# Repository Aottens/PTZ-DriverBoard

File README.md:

# PTZ driver board

A driver board for PTZ camera heads and its firmware, designed together: one print that can drive any head.

## Status
Rev B of the board is designed and checked, and ready for a JLC quote: a cheap two-layer carrier for plug-in
drivers, MCU and Ethernet, estimated at €68 to €90 for five assembled boards. It is not ordered and not measured.
Rev A, which would have cost almost €400, is under the git tag `rev-a`. There is no firmware yet.
The test rig for the mechanics is modelled, not printed.
Plan in `BACKLOG.md`, handoff in `STATE.md`, decisions in `DECISIONS.md`.

## What works today
- `hardware/`: the KiCad 10 project of Rev B, generated by the scripts in `hardware/tools/`, with BOM, placement file
  and Gerbers for JLCPCB in `hardware/fab/`. How to rebuild it: `hardware/README.md`. What to buy and solder:
  `hardware/ASSEMBLY.md`.
- Checks that run on any machine with KiCad 10: `hardware/check_netlist.py` (every pin against the specs),
  `hardware/check_board.py` (every number in `specs/modules/board.md`, ERC and DRC), `hardware/check_fit.py`
  (the board with its modules and plugs in the base).
- `hardware/calc/`: the power calculations and the cost estimate of one JLC order, from the real BOM.
- `tests/hardware/bringup-rev-b.md`: the current-limited first power-up, for the owner to run on the real board.
- `mechanica/rig/`: the test rig model and its checks.

## How work happens
Spec → test → build → review, one build per PR; see `CLAUDE.md`.

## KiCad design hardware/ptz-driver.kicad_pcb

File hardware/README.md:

# hardware/

The driver board, Rev B: a two-layer carrier for plug-in modules. The specs in `specs/modules/` say what each part
is for; this says how the files are made. Rev A, the four-layer board with its drivers on board, is under the git
tag `rev-a` (`git show rev-a:hardware/README.md`).

## What is where

| File | What |
| --- | --- |
| `ptz-driver.kicad_pro`, `.kicad_sch`, `.kicad_pcb` and the sheet files | The KiCad 10 project. Open it in KiCad to look; change it through the scripts |
| `tools/circuit.py` | The circuit as data: every part, net, footprint and LCSC number. Writes the schematic |
| `../firmware/include/pins.h` | The one place MCU pins are assigned |
| `tools/make_libs.py`, `ptz.pretty/` | The project's footprints: the three module sockets, the 5 V regulator, the test point |
| `tools/placement.py` | Where every part sits, and the copper laid before routing: the supply path, the motor outputs |
| `tools/board.py`, `tools/silk.py` | The board build (place, dsn, ses, finish) and the silkscreen |
| `route/run.sh`, `tools/complete.py`, `tools/widen.py` | Routing from scratch: Freerouting, then the grid router that closes what it leaves open and stitches the ground pours, then supply tracks widened where the routers necked them |
| `tools/project.py` | Design rules and net classes (KiCad rewrites the project file, so they live here) |
| `check_netlist.py` | Expected pin-to-net table per criterion, written from the specs without the schematic |
| `check_board.py` | Every number `specs/modules/board.md` states, plus ERC and DRC |
| `tools/groundcut.py` | The narrowest cross-section of ground copper between two groups of pads (BRD-13), used by `check_board.py` |
| `check_fit.py` | The board with its modules, heat sinks and plugs in the working envelope |
| `calc/power.py`, `calc/cost.py` | The calculations, with every input and its source |
| `fab/make_jlc.py`, `fab/jlc/`, `fab/gerbers/` | BOM and placement file fitted on JLC's own footprints, and the Gerbers |
| `fab/jlc_pins.py`, `fab/jlc_pins.md` | What JLC's own library calls each pin of every polar part, against the board's nets |
| `sourcing/` | JLC's parts API (`jlc_api.py`) and the check table per BOM line (`jlc_check.md`) |
| `sourcing/owner_bom.py`, `owner_bom.md`, `owner_bom_reichelt.csv` | The owner's shopping list for everything JLC does not assemble, from the schematic, with Reichelt's article numbers and prices |
| `review/` | The blind review and what was done with it |
| `ASSEMBLY.md`, `BUILD_NOTES.md`, `datasheets/README.md` | What the owner buys, solders and plugs; lessons; datasheet sources and revisions |

## Rebuilding from scratch

`KP` is KiCad's Python: `/Applications/KiCad/KiCad.app/Contents/Frameworks/Python.framework/Versions/Current/bin/python3`.
Run from `hardware/`.

1. `python3 tools/make_libs.py`: project footprints, library tables, project rules.
2. `python3 tools/circuit.py`: the schematic. It reads the netlist back through KiCad and stops if it differs.
3. `python3 check_netlist.py`
4. `sh route/run.sh`: places every part, routes, finishes the board and widens its supply tracks, about five minutes. **This discards the
   routing**, and Freerouting is not repeatable: a rerun gives another board. What was done by hand on the board
   in this repository afterwards is in `BUILD_NOTES.md` under *How the routed board was made*.
5. `$KP check_board.py` and `$KP check_fit.py`
6. `$KP fab/make_jlc.py`, `python3 sourcing/jlc_read.py`, `python3 fab/jlc_pins.py > fab/jlc_pins.md`,
   `python3 calc/cost.py`, and the Gerbers with `sh fab/make_gerbers.sh`.

A change that keeps the placement and the nets (a value, an LCSC number) needs only steps 2, 3 and 6, but the
footprint fields on the board then lag the schematic until step 4: `check_board.py` reports that as a parity
issue. `$KP tools/board.py finish` alone redraws the silkscreen and the top ground pour on the routed board.

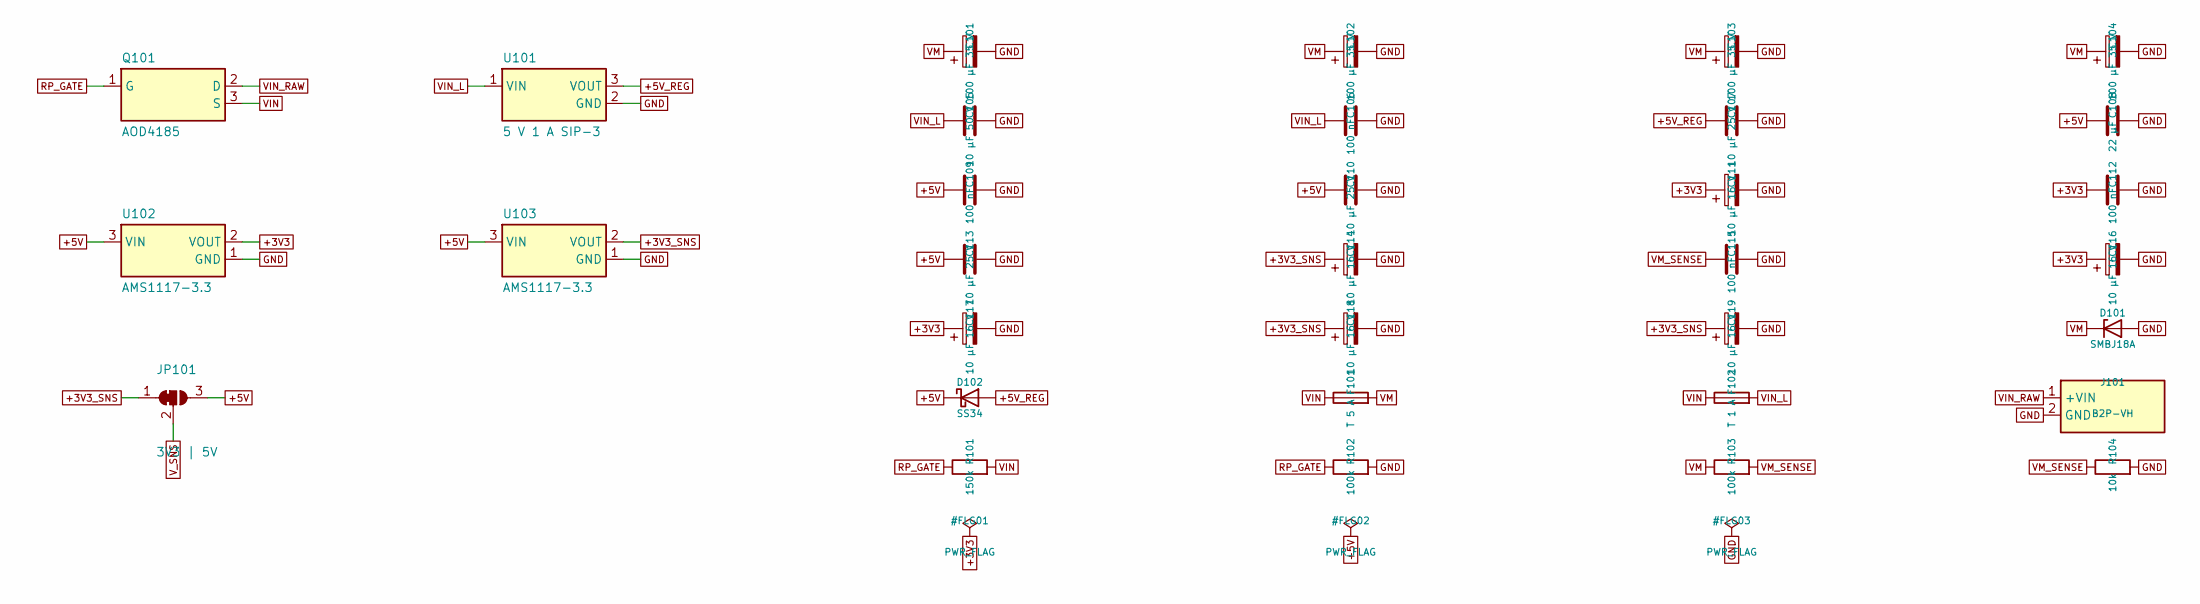
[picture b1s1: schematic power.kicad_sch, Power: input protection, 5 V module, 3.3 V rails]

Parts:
C101, C102, C103, C104: 100 µF 35 V; CP_Radial_D6.3mm_P2.50mm
C105: 10 µF 50 V; C_1206_3216Metric; LCSC C13585
C106, C109, C112, C115: 100 nF; C_0603_1608Metric; LCSC C14663
C107, C110, C113: 10 µF 25 V; C_0805_2012Metric; LCSC C15850
C108: 22 µF; C_0805_2012Metric; LCSC C45783
C111, C114, C116, C117, C118, C119: 10 µF 16 V; CP_EIA-3216-18_Kemet-A; MPN TAJA106K016RNJ; LCSC C7171
D101: SMBJ18A; D_SMB; MPN SMBJ18A; LCSC C19077573
D102: SS34; D_SMA; MPN SS34; LCSC C8678
F101: T 5 A; Fuseholder_TR5_Littelfuse_No560_No460
F102: T 1 A; Fuseholder_TR5_Littelfuse_No560_No460
J101: B2P-VH; JST_VH_B2P-VH_1x02_P3.96mm_Vertical
JP101: 3V3 | 5V; SolderJumper-3_P1.3mm_Bridged12_RoundedPad1.0x1.5mm
Q101: AOD4185; TO-252_JLC; MPN AOD4185; LCSC C400894
R101: 150k; R_0603_1608Metric; LCSC C22807
R102, R103: 100k; R_0603_1608Metric; LCSC C25803
R104: 10k; R_0603_1608Metric; LCSC C25804
U101: 5 V 1 A SIP-3; SIP3_DCDC_7805
U102, U103: AMS1117-3.3; SOT-223-3_TabPin2; MPN AMS1117-3.3; LCSC C6186

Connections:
+3V3: C111.1, C112.1, C116.1, C117.1, U102.2 (VOUT); also elsewhere on the board
+3V3_SNS: C114.1, C118.1, C119.1, JP101.1 (A), U103.2 (VOUT)
+5V_REG: C107.1, D102.2 (A), U101.3 (VOUT)
GND: C101.2, C102.2, C103.2, C104.2, C105.2, C106.2, C107.2, C108.2, C109.2, C110.2, C111.2, C112.2, C113.2, C114.2, C115.2, C116.2, C117.2, C118.2, C119.2, D101.2 (A), J101.2 (GND), R102.2, R104.2, U101.2 (GND), U102.1 (GND), U103.1 (GND); also elsewhere on the board
RP_GATE: Q101.1 (G), R101.1, R102.1
VIN: F101.1, F102.1, Q101.3 (S), R101.2; also elsewhere on the board
VIN_L: C105.1, C106.1, F102.2, U101.1 (VIN); also elsewhere on the board
VIN_RAW: J101.1 (+VIN), Q101.2 (D)
VM: C101.1, C102.1, C103.1, C104.1, D101.1 (K), F101.2, R103.1; also elsewhere on the board
VM_SENSE: C115.1, R103.2, R104.1; also elsewhere on the board
V_SNS: JP101.2 (C); also elsewhere on the board

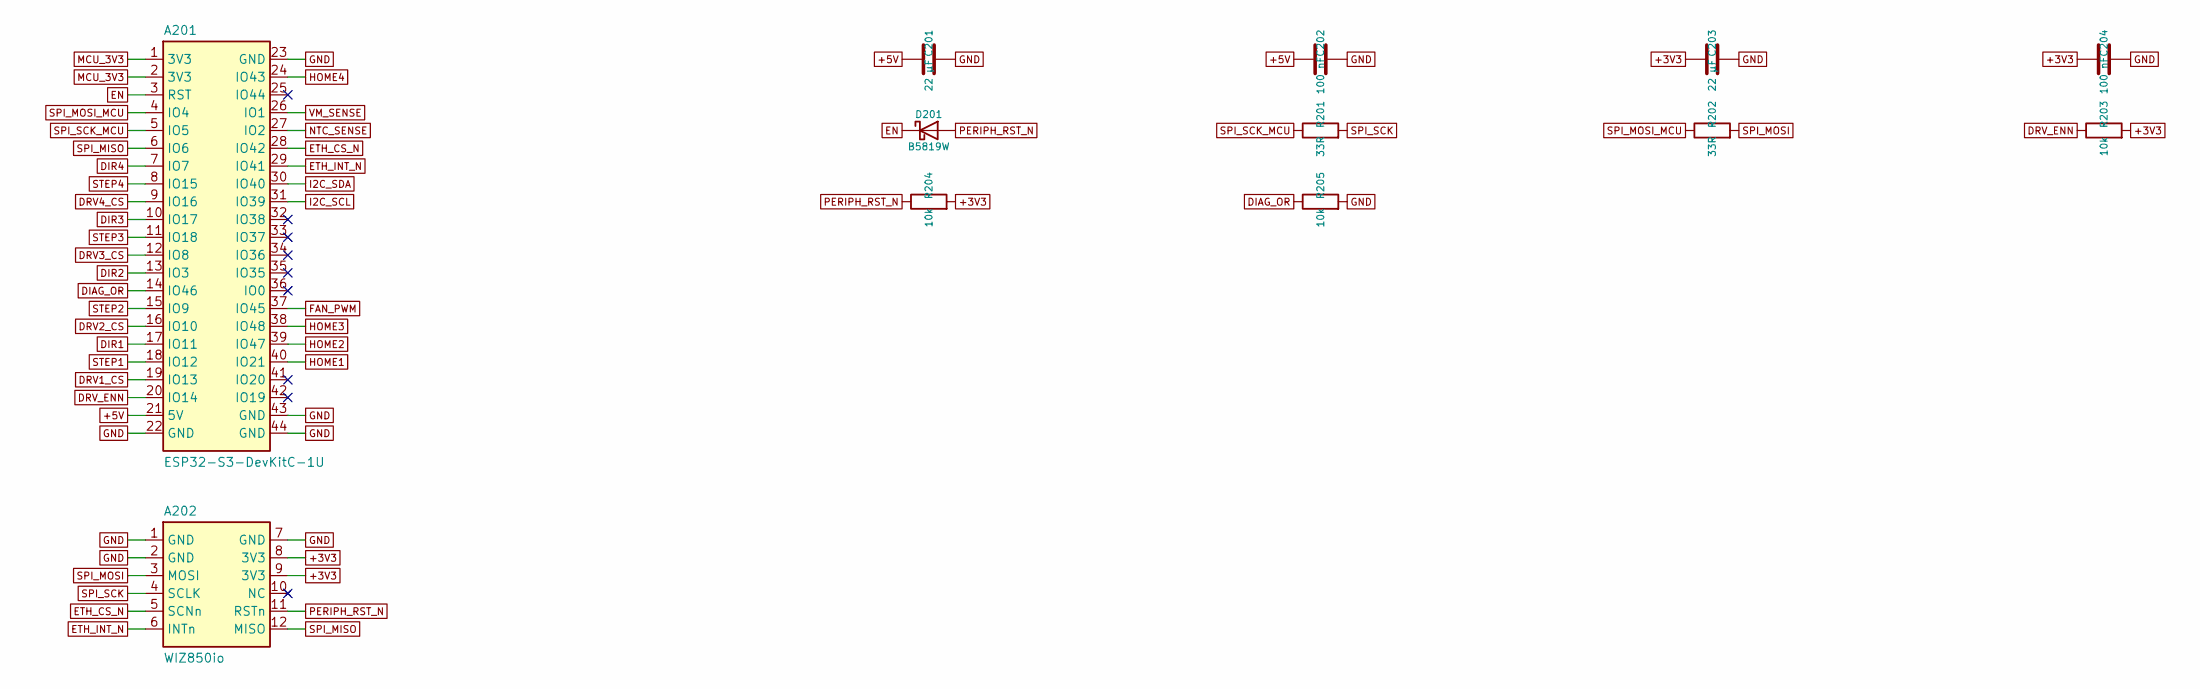
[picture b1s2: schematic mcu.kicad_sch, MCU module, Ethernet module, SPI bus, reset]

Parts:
A201: ESP32-S3-DevKitC-1U; ESP32-S3-DevKitC-1
A202: WIZ850io
C201, C203: 22 µF; C_0805_2012Metric; LCSC C45783
C202, C204: 100 nF; C_0603_1608Metric; LCSC C14663
D201: B5819W; D_SOD-123; MPN B5819W; LCSC C8598
R201, R202: 33R; R_0603_1608Metric; LCSC C23140
R203, R204, R205: 10k; R_0603_1608Metric; LCSC C25804

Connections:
+3V3: A202.8 (3V3), A202.9 (3V3), C203.1, C204.1, R203.2, R204.2; also elsewhere on the board
DIR1: A201.17 (IO11); also elsewhere on the board
DIR3: A201.10 (IO17); also elsewhere on the board
DIR4: A201.7 (IO7); also elsewhere on the board
DRV1_CS: A201.19 (IO13); also elsewhere on the board
DRV2_CS: A201.16 (IO10); also elsewhere on the board
DRV3_CS: A201.12 (IO8); also elsewhere on the board
DRV4_CS: A201.9 (IO16); also elsewhere on the board
DRV_ENN: A201.20 (IO14), R203.1; also elsewhere on the board
EN: A201.3 (RST), D201.1 (K)
ETH_CS_N: A201.28 (IO42), A202.5 (SCNn)
ETH_INT_N: A201.29 (IO41), A202.6 (INTn)
FAN_PWM: A201.37 (IO45); also elsewhere on the board
GND: A201.22 (GND), A201.23 (GND), A201.43 (GND), A201.44 (GND), A202.1 (GND), A202.2 (GND), A202.7 (GND), C201.2, C202.2, C203.2, C204.2, R205.2; also elsewhere on the board
HOME1: A201.40 (IO21); also elsewhere on the board
HOME2: A201.39 (IO47); also elsewhere on the board
HOME3: A201.38 (IO48); also elsewhere on the board
HOME4: A201.24 (IO43); also elsewhere on the board
I2C_SCL: A201.31 (IO39); also elsewhere on the board
I2C_SDA: A201.30 (IO40); also elsewhere on the board
MCU_3V3: A201.1 (3V3), A201.2 (3V3); also elsewhere on the board
NTC_SENSE: A201.27 (IO2); also elsewhere on the board
PERIPH_RST_N: A202.11 (RSTn), D201.2 (A), R204.1; also elsewhere on the board
SPI_MISO: A201.6 (IO6), A202.12 (MISO); also elsewhere on the board
SPI_MOSI: A202.3 (MOSI), R202.2; also elsewhere on the board
SPI_MOSI_MCU: A201.4 (IO4), R202.1
SPI_SCK: A202.4 (SCLK), R201.2; also elsewhere on the board
SPI_SCK_MCU: A201.5 (IO5), R201.1
STEP1: A201.18 (IO12); also elsewhere on the board
STEP2: A201.15 (IO9); also elsewhere on the board
STEP3: A201.11 (IO18); also elsewhere on the board
STEP4: A201.8 (IO15); also elsewhere on the board
VM_SENSE: A201.26 (IO1); also elsewhere on the board

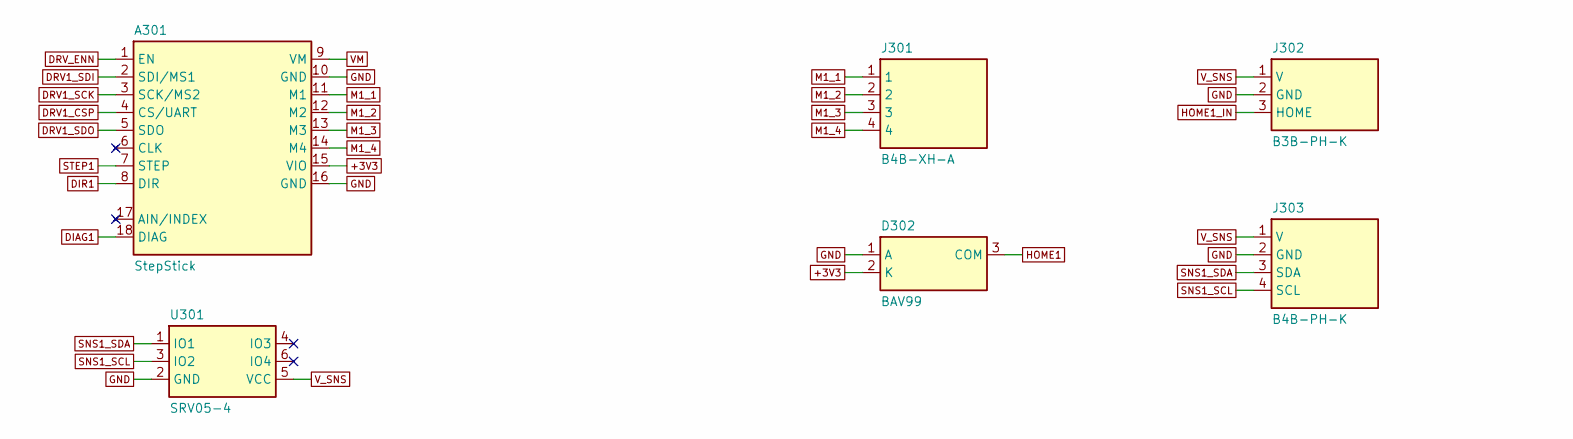
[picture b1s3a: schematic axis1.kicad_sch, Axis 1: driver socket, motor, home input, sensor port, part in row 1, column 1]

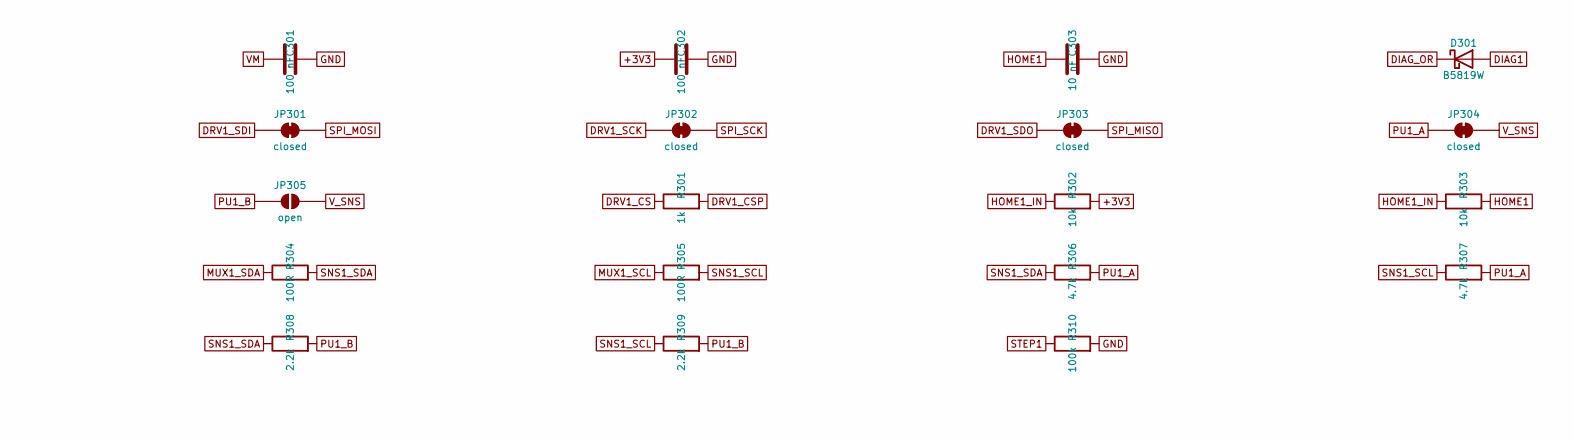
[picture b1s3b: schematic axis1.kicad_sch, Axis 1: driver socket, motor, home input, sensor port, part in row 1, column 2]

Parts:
A301: StepStick; StepStick_Socket
C301, C302: 100 nF; C_0603_1608Metric; LCSC C14663
C303: 10 nF; C_0603_1608Metric; LCSC C57112
D301: B5819W; D_SOD-123; MPN B5819W; LCSC C8598
D302: BAV99; SOT-23; MPN BAV99,215; LCSC C2500
J301: B4B-XH-A; JST_XH_B4B-XH-A_1x04_P2.50mm_Vertical
J302: B3B-PH-K; JST_PH_B3B-PH-K_1x03_P2.00mm_Vertical
J303: B4B-PH-K; JST_PH_B4B-PH-K_1x04_P2.00mm_Vertical
JP301, JP302, JP303, JP304: closed; SolderJumper-2_P1.3mm_Bridged_RoundedPad1.0x1.5mm
JP305: open; SolderJumper-2_P1.3mm_Open_RoundedPad1.0x1.5mm
R301: 1k; R_0603_1608Metric; LCSC C21190
R302, R303: 10k; R_0603_1608Metric; LCSC C25804
R304, R305: 100R; R_0603_1608Metric; LCSC C22775
R306, R307: 4.7k; R_0603_1608Metric; LCSC C23162
R308, R309: 2.2k; R_0603_1608Metric; LCSC C4190
R310: 100k; R_0603_1608Metric; LCSC C25803
U301: SRV05-4; SOT-23-6; MPN SRV05-4; LCSC C7420376

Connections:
+3V3: A301.15 (VIO), C302.1, D302.2 (K), R302.2; also elsewhere on the board
DIAG1: A301.18 (DIAG), D301.2 (A)
DIR1: A301.8 (DIR); also elsewhere on the board
DRV1_CS: R301.1; also elsewhere on the board
DRV1_CSP: A301.4 (CS/UART), R301.2
DRV1_SCK: A301.3 (SCK/MS2), JP302.1 (A)
DRV1_SDI: A301.2 (SDI/MS1), JP301.1 (A)
DRV1_SDO: A301.5 (SDO), JP303.1 (A)
DRV_ENN: A301.1 (EN); also elsewhere on the board
GND: A301.10 (GND), A301.16 (GND), C301.2, C302.2, C303.2, D302.1 (A), J302.2 (GND), J303.2 (GND), R310.2, U301.2 (GND); also elsewhere on the board
HOME1: C303.1, D302.3 (COM), R303.2; also elsewhere on the board
HOME1_IN: J302.3 (HOME), R302.1, R303.1
M1_1: A301.11 (M1), J301.1
M1_2: A301.12 (M2), J301.2
M1_3: A301.13 (M3), J301.3
M1_4: A301.14 (M4), J301.4
MUX1_SCL: R305.1; also elsewhere on the board
MUX1_SDA: R304.1; also elsewhere on the board
PU1_A: JP304.1 (A), R306.2, R307.2
PU1_B: JP305.1 (A), R308.2, R309.2
SNS1_SCL: J303.4 (SCL), R305.2, R307.1, R309.1, U301.3 (IO2)
SNS1_SDA: J303.3 (SDA), R304.2, R306.1, R308.1, U301.1 (IO1)
SPI_MISO: JP303.2 (B); also elsewhere on the board
SPI_MOSI: JP301.2 (B); also elsewhere on the board
SPI_SCK: JP302.2 (B); also elsewhere on the board
STEP1: A301.7 (STEP), R310.1; also elsewhere on the board
VM: A301.9 (VM), C301.1; also elsewhere on the board
V_SNS: J302.1 (V), J303.1 (V), JP304.2 (B), JP305.2 (B), U301.5 (VCC); also elsewhere on the board

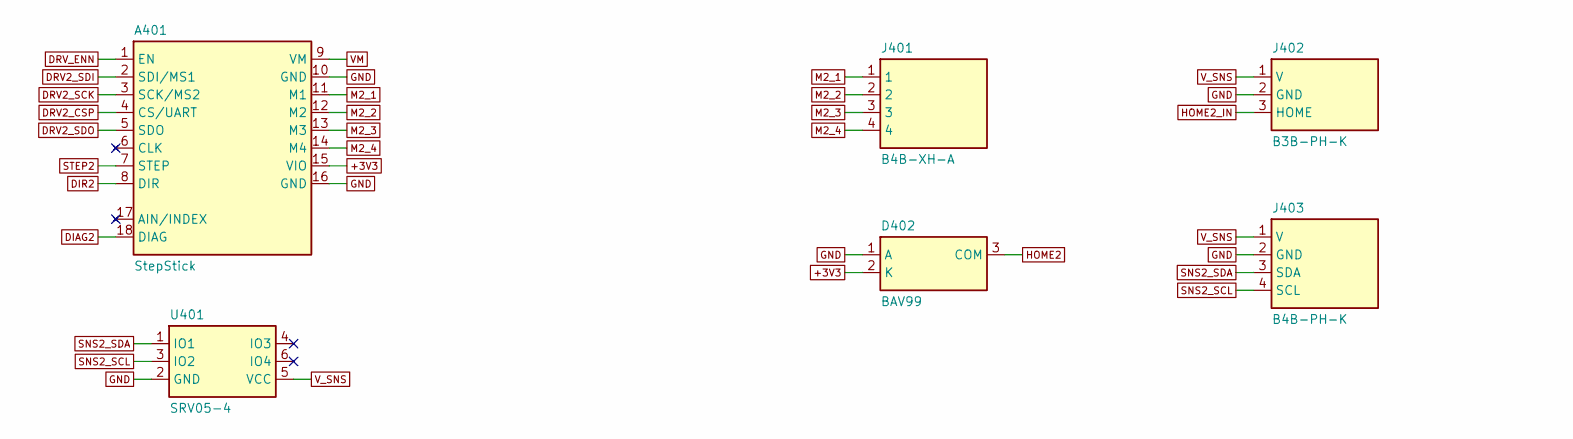
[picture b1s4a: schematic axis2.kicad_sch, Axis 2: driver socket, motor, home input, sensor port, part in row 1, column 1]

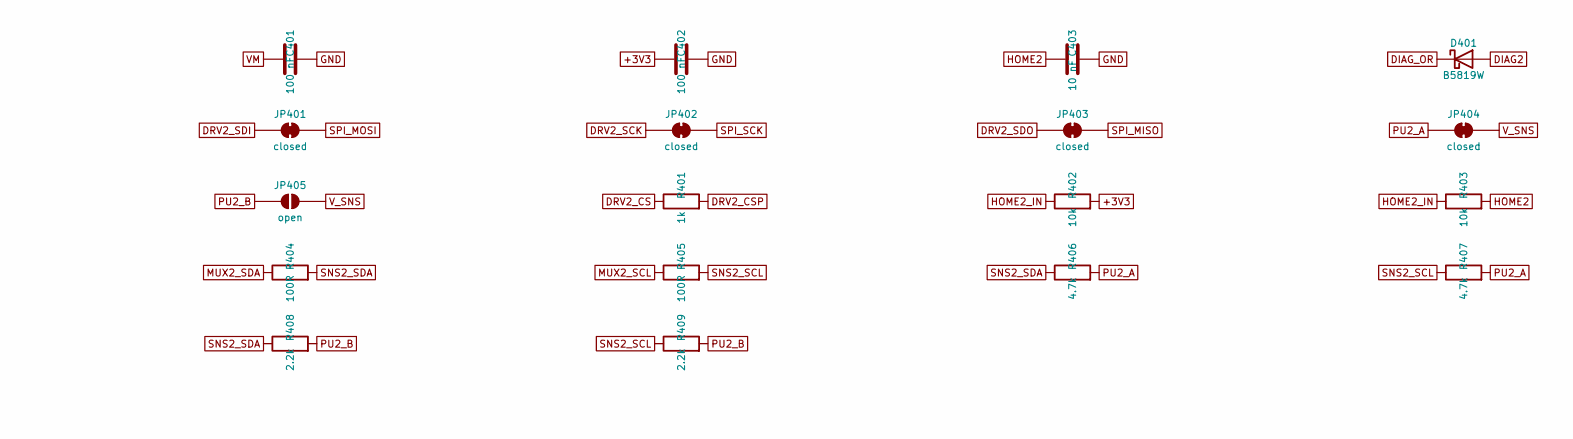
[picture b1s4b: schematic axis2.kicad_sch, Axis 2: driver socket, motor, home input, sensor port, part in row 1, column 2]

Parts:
A401: StepStick; StepStick_Socket
C401, C402: 100 nF; C_0603_1608Metric; LCSC C14663
C403: 10 nF; C_0603_1608Metric; LCSC C57112
D401: B5819W; D_SOD-123; MPN B5819W; LCSC C8598
D402: BAV99; SOT-23; MPN BAV99,215; LCSC C2500
J401: B4B-XH-A; JST_XH_B4B-XH-A_1x04_P2.50mm_Vertical
J402: B3B-PH-K; JST_PH_B3B-PH-K_1x03_P2.00mm_Vertical
J403: B4B-PH-K; JST_PH_B4B-PH-K_1x04_P2.00mm_Vertical
JP401, JP402, JP403, JP404: closed; SolderJumper-2_P1.3mm_Bridged_RoundedPad1.0x1.5mm
JP405: open; SolderJumper-2_P1.3mm_Open_RoundedPad1.0x1.5mm
R401: 1k; R_0603_1608Metric; LCSC C21190
R402, R403: 10k; R_0603_1608Metric; LCSC C25804
R404, R405: 100R; R_0603_1608Metric; LCSC C22775
R406, R407: 4.7k; R_0603_1608Metric; LCSC C23162
R408, R409: 2.2k; R_0603_1608Metric; LCSC C4190
U401: SRV05-4; SOT-23-6; MPN SRV05-4; LCSC C7420376

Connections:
+3V3: A401.15 (VIO), C402.1, D402.2 (K), R402.2; also elsewhere on the board
DIAG2: A401.18 (DIAG), D401.2 (A)
DRV2_CS: R401.1; also elsewhere on the board
DRV2_CSP: A401.4 (CS/UART), R401.2
DRV2_SCK: A401.3 (SCK/MS2), JP402.1 (A)
DRV2_SDI: A401.2 (SDI/MS1), JP401.1 (A)
DRV2_SDO: A401.5 (SDO), JP403.1 (A)
DRV_ENN: A401.1 (EN); also elsewhere on the board
GND: A401.10 (GND), A401.16 (GND), C401.2, C402.2, C403.2, D402.1 (A), J402.2 (GND), J403.2 (GND), U401.2 (GND); also elsewhere on the board
HOME2: C403.1, D402.3 (COM), R403.2; also elsewhere on the board
HOME2_IN: J402.3 (HOME), R402.1, R403.1
M2_1: A401.11 (M1), J401.1
M2_2: A401.12 (M2), J401.2
M2_3: A401.13 (M3), J401.3
M2_4: A401.14 (M4), J401.4
MUX2_SCL: R405.1; also elsewhere on the board
MUX2_SDA: R404.1; also elsewhere on the board
PU2_A: JP404.1 (A), R406.2, R407.2
PU2_B: JP405.1 (A), R408.2, R409.2
SNS2_SCL: J403.4 (SCL), R405.2, R407.1, R409.1, U401.3 (IO2)
SNS2_SDA: J403.3 (SDA), R404.2, R406.1, R408.1, U401.1 (IO1)
SPI_MISO: JP403.2 (B); also elsewhere on the board
SPI_MOSI: JP401.2 (B); also elsewhere on the board
SPI_SCK: JP402.2 (B); also elsewhere on the board
STEP2: A401.7 (STEP); also elsewhere on the board
VM: A401.9 (VM), C401.1; also elsewhere on the board
V_SNS: J402.1 (V), J403.1 (V), JP404.2 (B), JP405.2 (B), U401.5 (VCC); also elsewhere on the board

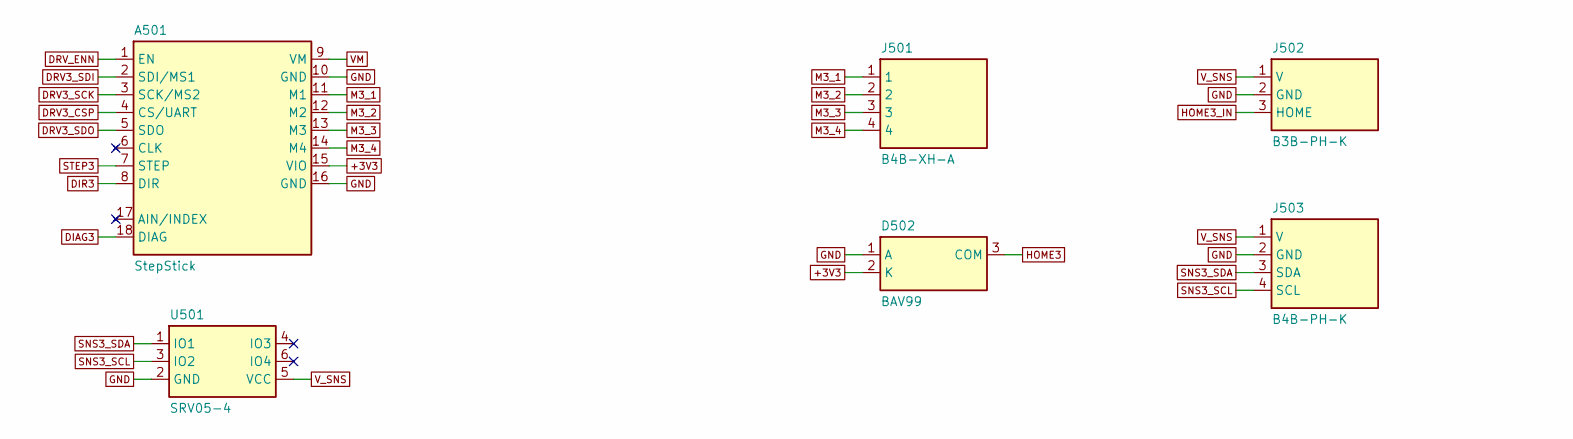
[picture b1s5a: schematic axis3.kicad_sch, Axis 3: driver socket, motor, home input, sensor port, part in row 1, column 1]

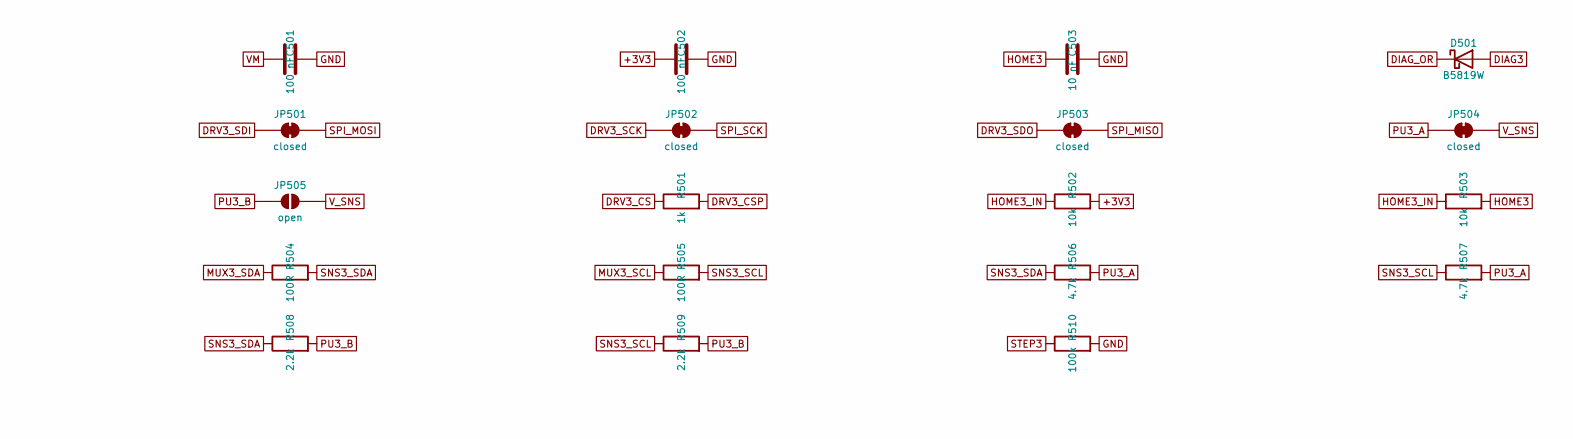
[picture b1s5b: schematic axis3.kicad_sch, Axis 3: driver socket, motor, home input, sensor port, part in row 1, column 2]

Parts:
A501: StepStick; StepStick_Socket
C501, C502: 100 nF; C_0603_1608Metric; LCSC C14663
C503: 10 nF; C_0603_1608Metric; LCSC C57112
D501: B5819W; D_SOD-123; MPN B5819W; LCSC C8598
D502: BAV99; SOT-23; MPN BAV99,215; LCSC C2500
J501: B4B-XH-A; JST_XH_B4B-XH-A_1x04_P2.50mm_Vertical
J502: B3B-PH-K; JST_PH_B3B-PH-K_1x03_P2.00mm_Vertical
J503: B4B-PH-K; JST_PH_B4B-PH-K_1x04_P2.00mm_Vertical
JP501, JP502, JP503, JP504: closed; SolderJumper-2_P1.3mm_Bridged_RoundedPad1.0x1.5mm
JP505: open; SolderJumper-2_P1.3mm_Open_RoundedPad1.0x1.5mm
R501: 1k; R_0603_1608Metric; LCSC C21190
R502, R503: 10k; R_0603_1608Metric; LCSC C25804
R504, R505: 100R; R_0603_1608Metric; LCSC C22775
R506, R507: 4.7k; R_0603_1608Metric; LCSC C23162
R508, R509: 2.2k; R_0603_1608Metric; LCSC C4190
R510: 100k; R_0603_1608Metric; LCSC C25803
U501: SRV05-4; SOT-23-6; MPN SRV05-4; LCSC C7420376

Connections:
+3V3: A501.15 (VIO), C502.1, D502.2 (K), R502.2; also elsewhere on the board
DIAG3: A501.18 (DIAG), D501.2 (A)
DIR3: A501.8 (DIR); also elsewhere on the board
DRV3_CS: R501.1; also elsewhere on the board
DRV3_CSP: A501.4 (CS/UART), R501.2
DRV3_SCK: A501.3 (SCK/MS2), JP502.1 (A)
DRV3_SDI: A501.2 (SDI/MS1), JP501.1 (A)
DRV3_SDO: A501.5 (SDO), JP503.1 (A)
DRV_ENN: A501.1 (EN); also elsewhere on the board
GND: A501.10 (GND), A501.16 (GND), C501.2, C502.2, C503.2, D502.1 (A), J502.2 (GND), J503.2 (GND), R510.2, U501.2 (GND); also elsewhere on the board
HOME3: C503.1, D502.3 (COM), R503.2; also elsewhere on the board
HOME3_IN: J502.3 (HOME), R502.1, R503.1
M3_1: A501.11 (M1), J501.1
M3_2: A501.12 (M2), J501.2
M3_3: A501.13 (M3), J501.3
M3_4: A501.14 (M4), J501.4
MUX3_SCL: R505.1; also elsewhere on the board
MUX3_SDA: R504.1; also elsewhere on the board
PU3_A: JP504.1 (A), R506.2, R507.2
PU3_B: JP505.1 (A), R508.2, R509.2
SNS3_SCL: J503.4 (SCL), R505.2, R507.1, R509.1, U501.3 (IO2)
SNS3_SDA: J503.3 (SDA), R504.2, R506.1, R508.1, U501.1 (IO1)
SPI_MISO: JP503.2 (B); also elsewhere on the board
SPI_MOSI: JP501.2 (B); also elsewhere on the board
SPI_SCK: JP502.2 (B); also elsewhere on the board
STEP3: A501.7 (STEP), R510.1; also elsewhere on the board
VM: A501.9 (VM), C501.1; also elsewhere on the board
V_SNS: J502.1 (V), J503.1 (V), JP504.2 (B), JP505.2 (B), U501.5 (VCC); also elsewhere on the board

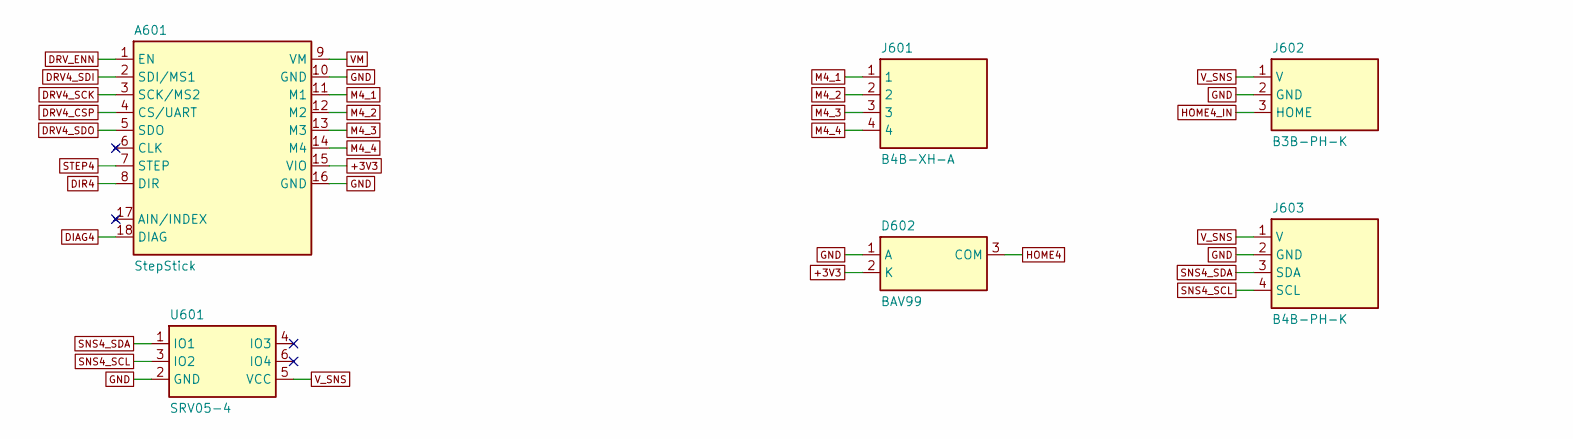
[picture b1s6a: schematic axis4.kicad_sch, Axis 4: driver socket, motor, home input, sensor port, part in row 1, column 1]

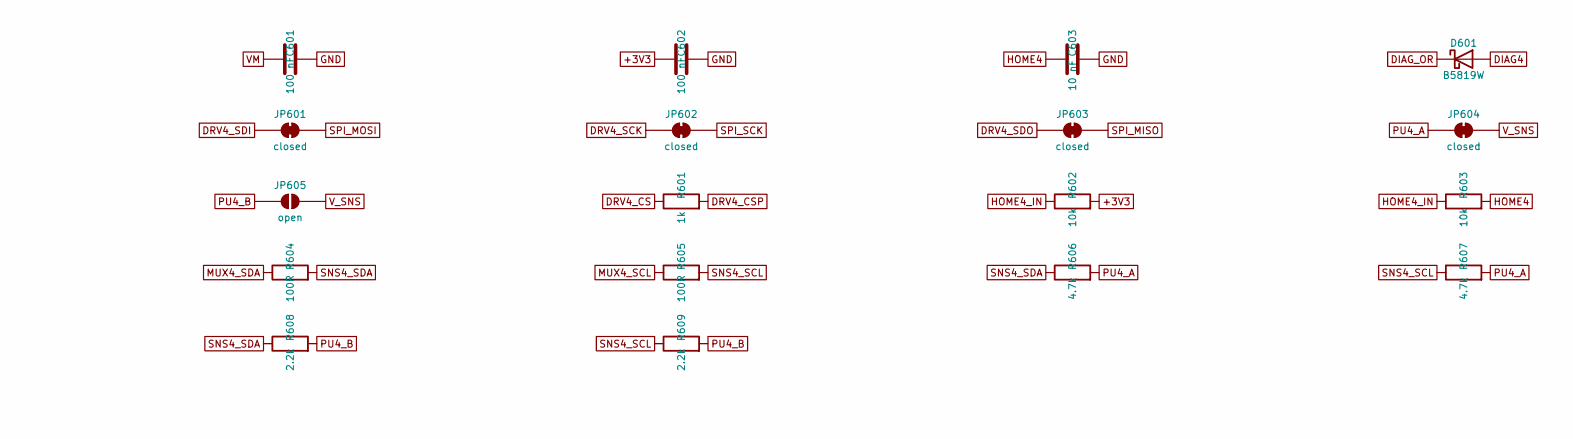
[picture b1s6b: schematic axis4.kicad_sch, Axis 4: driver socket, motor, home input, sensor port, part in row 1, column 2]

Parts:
A601: StepStick; StepStick_Socket
C601, C602: 100 nF; C_0603_1608Metric; LCSC C14663
C603: 10 nF; C_0603_1608Metric; LCSC C57112
D601: B5819W; D_SOD-123; MPN B5819W; LCSC C8598
D602: BAV99; SOT-23; MPN BAV99,215; LCSC C2500
J601: B4B-XH-A; JST_XH_B4B-XH-A_1x04_P2.50mm_Vertical
J602: B3B-PH-K; JST_PH_B3B-PH-K_1x03_P2.00mm_Vertical
J603: B4B-PH-K; JST_PH_B4B-PH-K_1x04_P2.00mm_Vertical
JP601, JP602, JP603, JP604: closed; SolderJumper-2_P1.3mm_Bridged_RoundedPad1.0x1.5mm
JP605: open; SolderJumper-2_P1.3mm_Open_RoundedPad1.0x1.5mm
R601: 1k; R_0603_1608Metric; LCSC C21190
R602, R603: 10k; R_0603_1608Metric; LCSC C25804
R604, R605: 100R; R_0603_1608Metric; LCSC C22775
R606, R607: 4.7k; R_0603_1608Metric; LCSC C23162
R608, R609: 2.2k; R_0603_1608Metric; LCSC C4190
U601: SRV05-4; SOT-23-6; MPN SRV05-4; LCSC C7420376

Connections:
+3V3: A601.15 (VIO), C602.1, D602.2 (K), R602.2; also elsewhere on the board
DIAG4: A601.18 (DIAG), D601.2 (A)
DIR4: A601.8 (DIR); also elsewhere on the board
DRV4_CS: R601.1; also elsewhere on the board
DRV4_CSP: A601.4 (CS/UART), R601.2
DRV4_SCK: A601.3 (SCK/MS2), JP602.1 (A)
DRV4_SDI: A601.2 (SDI/MS1), JP601.1 (A)
DRV4_SDO: A601.5 (SDO), JP603.1 (A)
DRV_ENN: A601.1 (EN); also elsewhere on the board
GND: A601.10 (GND), A601.16 (GND), C601.2, C602.2, C603.2, D602.1 (A), J602.2 (GND), J603.2 (GND), U601.2 (GND); also elsewhere on the board
HOME4: C603.1, D602.3 (COM), R603.2; also elsewhere on the board
HOME4_IN: J602.3 (HOME), R602.1, R603.1
M4_1: A601.11 (M1), J601.1
M4_2: A601.12 (M2), J601.2
M4_3: A601.13 (M3), J601.3
M4_4: A601.14 (M4), J601.4
MUX4_SCL: R605.1; also elsewhere on the board
MUX4_SDA: R604.1; also elsewhere on the board
PU4_A: JP604.1 (A), R606.2, R607.2
PU4_B: JP605.1 (A), R608.2, R609.2
SNS4_SCL: J603.4 (SCL), R605.2, R607.1, R609.1, U601.3 (IO2)
SNS4_SDA: J603.3 (SDA), R604.2, R606.1, R608.1, U601.1 (IO1)
SPI_MISO: JP603.2 (B); also elsewhere on the board
SPI_MOSI: JP601.2 (B); also elsewhere on the board
SPI_SCK: JP602.2 (B); also elsewhere on the board
STEP4: A601.7 (STEP); also elsewhere on the board
VM: A601.9 (VM), C601.1; also elsewhere on the board
V_SNS: J602.1 (V), J603.1 (V), JP604.2 (B), JP605.2 (B), U601.5 (VCC); also elsewhere on the board

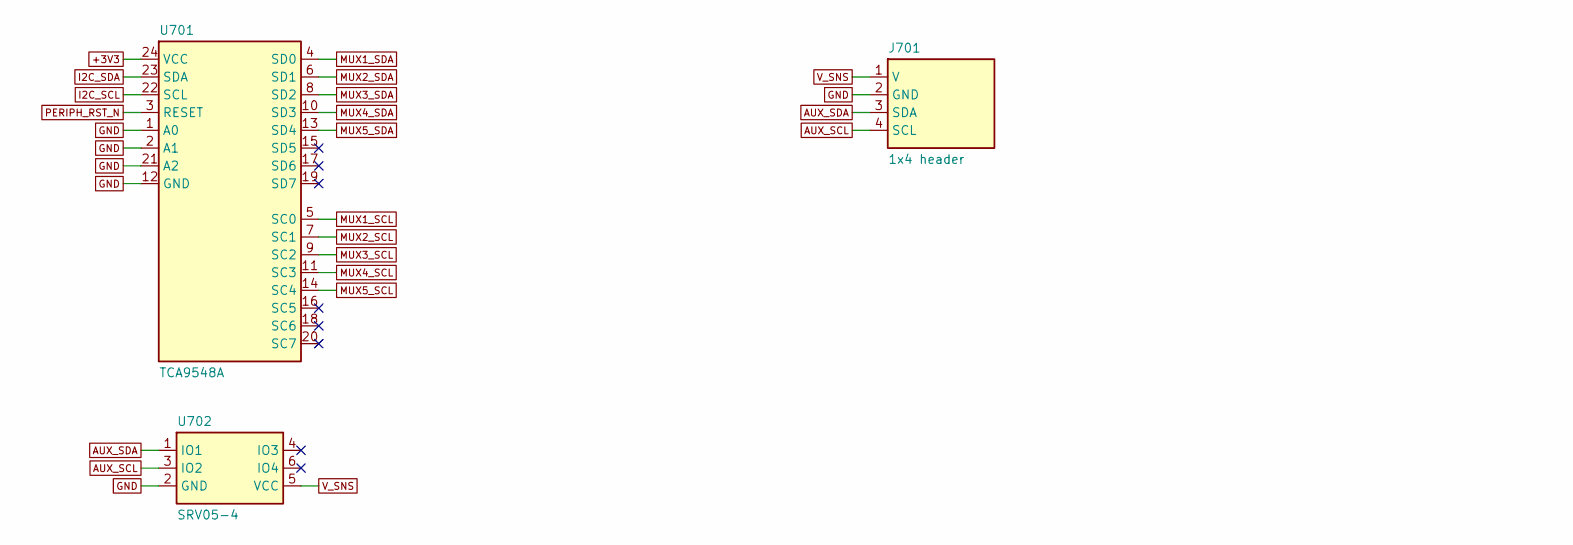
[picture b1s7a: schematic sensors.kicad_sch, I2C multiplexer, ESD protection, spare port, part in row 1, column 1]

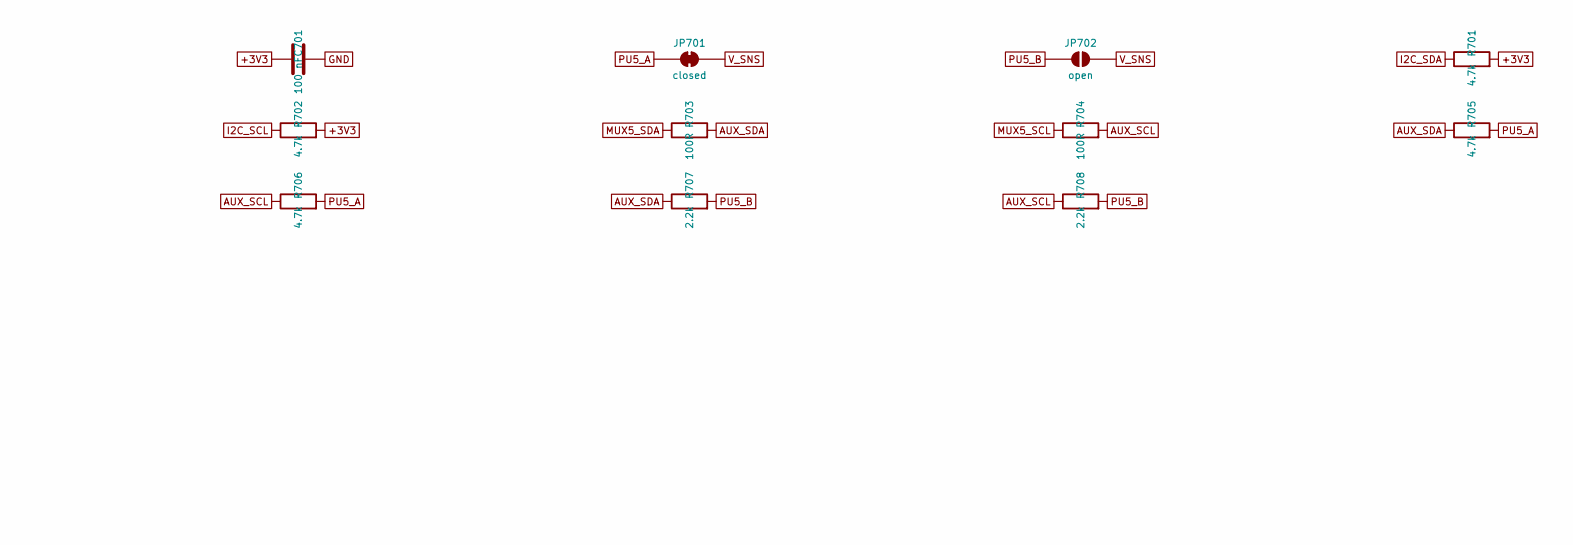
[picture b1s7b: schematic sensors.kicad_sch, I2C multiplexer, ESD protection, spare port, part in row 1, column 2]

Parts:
C701: 100 nF; C_0603_1608Metric; LCSC C14663
J701: 1x4 header; PinHeader_1x04_P2.54mm_Vertical
JP701: closed; SolderJumper-2_P1.3mm_Bridged_RoundedPad1.0x1.5mm
JP702: open; SolderJumper-2_P1.3mm_Open_RoundedPad1.0x1.5mm
R701, R702, R705, R706: 4.7k; R_0603_1608Metric; LCSC C23162
R703, R704: 100R; R_0603_1608Metric; LCSC C22775
R707, R708: 2.2k; R_0603_1608Metric; LCSC C4190
U701: TCA9548A; TSSOP-24_4.4x7.8mm_P0.65mm; MPN TCA9548APWR; LCSC C130026
U702: SRV05-4; SOT-23-6; MPN SRV05-4; LCSC C7420376

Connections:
+3V3: C701.1, R701.2, R702.2, U701.24 (VCC); also elsewhere on the board
AUX_SCL: J701.4 (SCL), R704.2, R706.1, R708.1, U702.3 (IO2)
AUX_SDA: J701.3 (SDA), R703.2, R705.1, R707.1, U702.1 (IO1)
GND: C701.2, J701.2 (GND), U701.1 (A0), U701.2 (A1), U701.12 (GND), U701.21 (A2), U702.2 (GND); also elsewhere on the board
I2C_SCL: R702.1, U701.22 (SCL); also elsewhere on the board
I2C_SDA: R701.1, U701.23 (SDA); also elsewhere on the board
MUX1_SCL: U701.5 (SC0); also elsewhere on the board
MUX1_SDA: U701.4 (SD0); also elsewhere on the board
MUX2_SCL: U701.7 (SC1); also elsewhere on the board
MUX2_SDA: U701.6 (SD1); also elsewhere on the board
MUX3_SCL: U701.9 (SC2); also elsewhere on the board
MUX3_SDA: U701.8 (SD2); also elsewhere on the board
MUX4_SCL: U701.11 (SC3); also elsewhere on the board
MUX4_SDA: U701.10 (SD3); also elsewhere on the board
MUX5_SCL: R704.1, U701.14 (SC4)
MUX5_SDA: R703.1, U701.13 (SD4)
PERIPH_RST_N: U701.3 (RESET); also elsewhere on the board
PU5_A: JP701.1 (A), R705.2, R706.2
PU5_B: JP702.1 (A), R707.2, R708.2
V_SNS: J701.1 (V), JP701.2 (B), JP702.2 (B), U702.5 (VCC); also elsewhere on the board
